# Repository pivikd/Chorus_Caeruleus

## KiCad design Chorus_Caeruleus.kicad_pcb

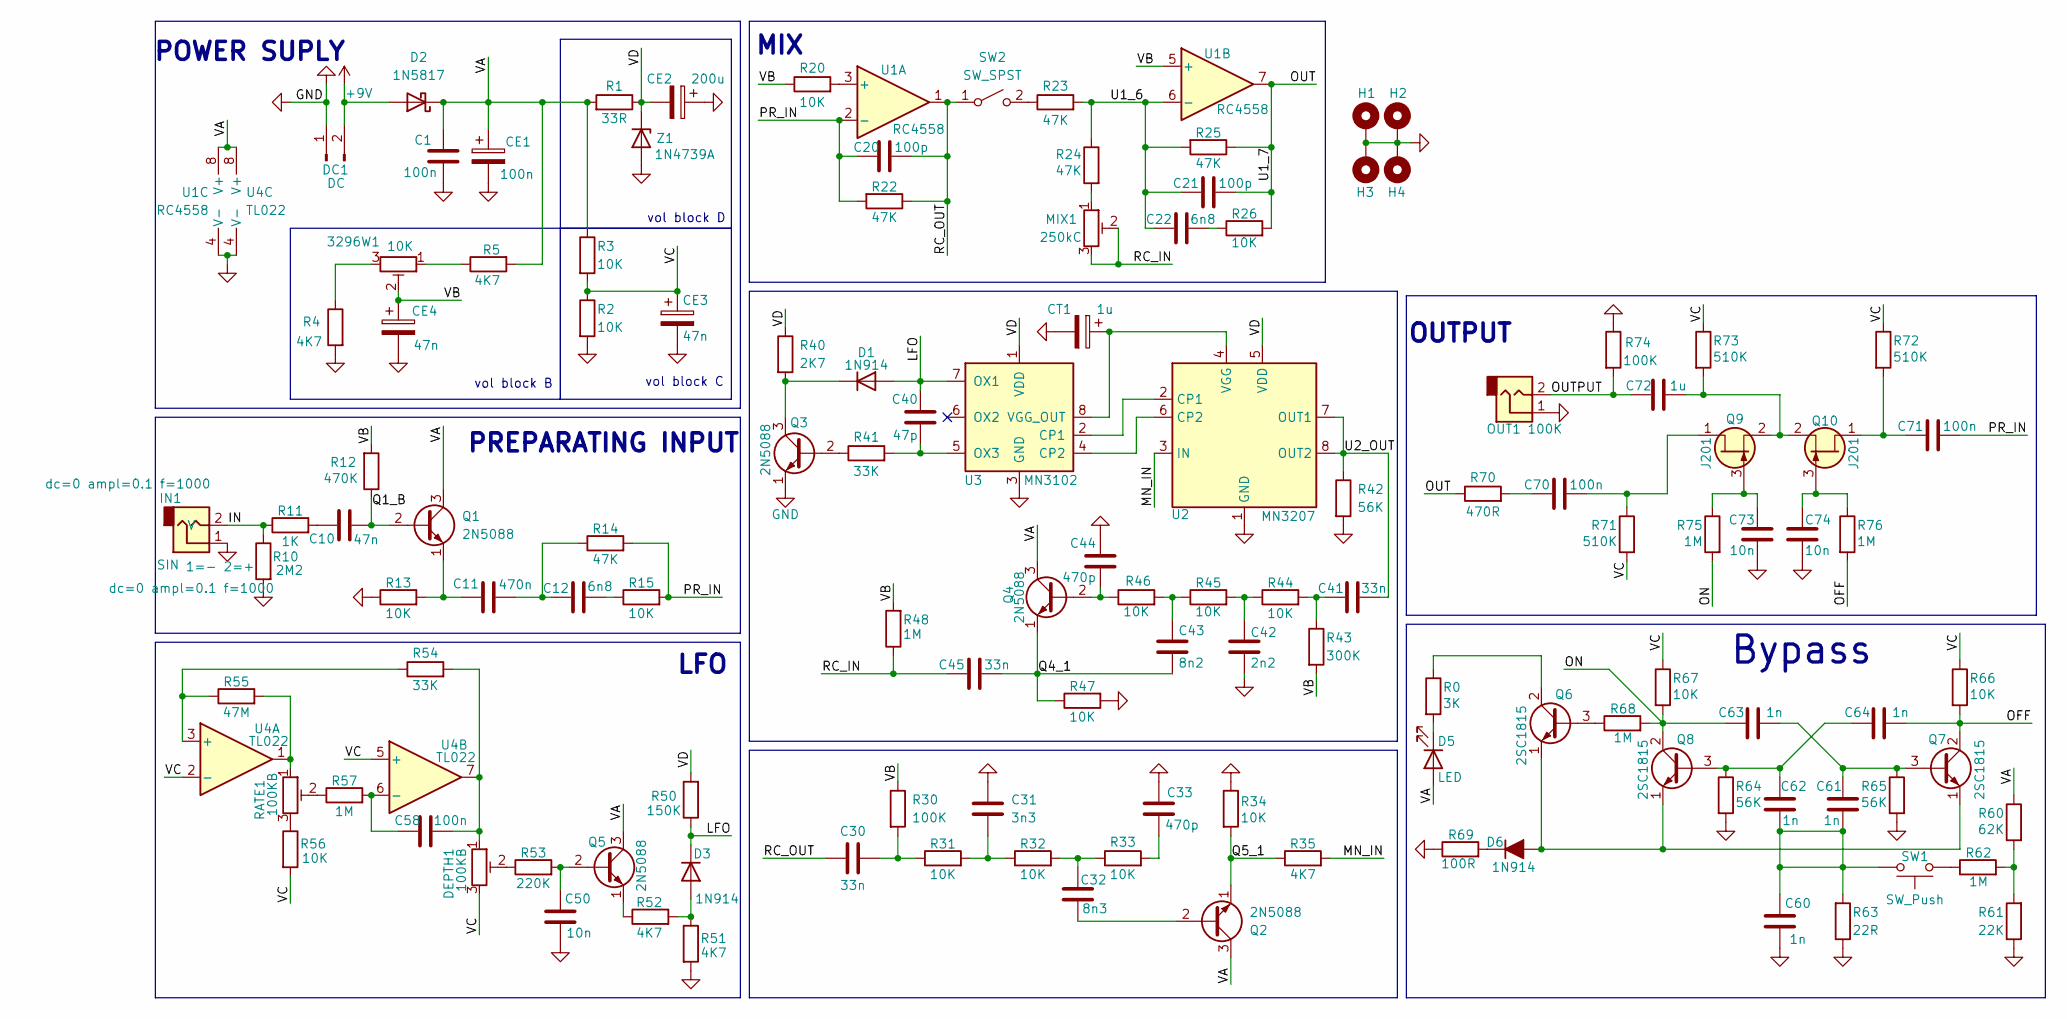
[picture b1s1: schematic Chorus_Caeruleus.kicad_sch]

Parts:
3296W1: 10K; Potentiometer_Bourns_3296W_Vertical
C1, C58, C70, C71: 100n; C_disc_D7_W2.5_P5
C10: 47n; C_Disc_D4.3_W1.9_P5.00
C11: 470n; C_disc_D7_W2.5_P5
C12, C22: 6n8; C_Disc_D4.3_W1.9_P5.00
C20, C21: 100p; C_Disc_D4.3_W1.9_P5.00
C30, C41, C45: 33n; C_Disc_D4.3_W1.9_P5.00
C31: 3n3; C_Disc_D4.3_W1.9_P5.00
C32: 8n3; C_Disc_D4.3_W1.9_P5.00
C33, C44: 470p; C_Disc_D4.3_W1.9_P5.00
C40: 47p; C_Disc_D4.3_W1.9_P5.00
C42: 2n2; C_Disc_D4.3_W1.9_P5.00
C43: 8n2; C_Disc_D4.3_W1.9_P5.00
C50, C73, C74: 10n; C_Disc_D4.3_W1.9_P5.00
C60, C61, C62, C63, C64: 1n; C_Disc_D4.3_W1.9_P5.00
C72: 1u; C_Disc_D4.3_W1.9_P5.00
CE1: 100n; CP_Radial_D4.0mm_P1.50mm
CE2: 200u; CP_Radial_D6.3mm_P2.50mm
CE3, CE4: 47n; CP_Radial_D4.0mm_P1.50mm
CT1: 1u; CP_Radial_Tantal_D5.0mm_P2.50mm
D1, D3, D6: 1N914; D_DO-35_SOD27_P7.62mm_Horizontal
D2: 1N5817; D_DO-41_SOD81_P10.16mm_Horizontal
D5: LED; PinHeader_1x02_P2.00mm_Vertical
DC1: DC; PinSocket_1x02_P2.00mm_Vertical
DEPTH1: 100KB; TO-92S
H1, H2, H3, H4: MountingHole_Pad; MountingHole_3.2mm_M3_ISO14580_Pad
IN1: dc=0 ampl=0.1 f=1000; PinHeader_1x02_P2.00mm_Vertical
MIX1: 250kC; TO-92S
OUT1: 100K; PinHeader_1x02_P2.00mm_Vertical
Q1, Q2, Q3, Q4, Q5: 2N5088; TO-92_Inline
Q6, Q7, Q8: 2SC1815; TO-92_Inline
Q9, Q10: J201; TO-92
R0: 3K; R_Axial_DIN0207_L6.3mm_D2.5mm_P7.62mm_Horizontal
R1: 33R; R_Axial_DIN0207_L6.3mm_D2.5mm_P7.62mm_Horizontal
R2, R3, R13, R15, R20, R26, R31, R32, R33, R34, R44, R45, R46, R47, R56, R66, R67: 10K; R_Axial_DIN0207_L6.3mm_D2.5mm_P7.62mm_Horizontal
R4, R5, R35, R51, R52: 4K7; R_Axial_DIN0207_L6.3mm_D2.5mm_P7.62mm_Horizontal
R10: 2M2; R_Axial_DIN0207_L6.3mm_D2.5mm_P7.62mm_Horizontal
R11: 1K; R_Axial_DIN0207_L6.3mm_D2.5mm_P7.62mm_Horizontal
R12: 470K; R_Axial_DIN0207_L6.3mm_D2.5mm_P7.62mm_Horizontal
R14, R22, R23, R24, R25: 47K; R_Axial_DIN0207_L6.3mm_D2.5mm_P7.62mm_Horizontal
R30, R74: 100K; R_Axial_DIN0207_L6.3mm_D2.5mm_P7.62mm_Horizontal
R40: 2K7; R_Axial_DIN0207_L6.3mm_D2.5mm_P7.62mm_Horizontal
R41, R54: 33K; R_Axial_DIN0207_L6.3mm_D2.5mm_P7.62mm_Horizontal
R42, R64, R65: 56K; R_Axial_DIN0207_L6.3mm_D2.5mm_P7.62mm_Horizontal
R43: 300K; R_Axial_DIN0207_L6.3mm_D2.5mm_P7.62mm_Horizontal
R48, R57, R62, R68, R75, R76: 1M; R_Axial_DIN0207_L6.3mm_D2.5mm_P7.62mm_Horizontal
R50: 150K; R_Axial_DIN0207_L6.3mm_D2.5mm_P7.62mm_Horizontal
R53: 220K; R_Axial_DIN0207_L6.3mm_D2.5mm_P7.62mm_Horizontal
R55: 47M; R_Axial_DIN0207_L6.3mm_D2.5mm_P7.62mm_Horizontal
R60: 62K; R_Axial_DIN0207_L6.3mm_D2.5mm_P7.62mm_Horizontal
R61: 22K; R_Axial_DIN0207_L6.3mm_D2.5mm_P7.62mm_Horizontal
R63: 22R; R_Axial_DIN0207_L6.3mm_D2.5mm_P7.62mm_Horizontal
R69: 100R; R_Axial_DIN0207_L6.3mm_D2.5mm_P7.62mm_Horizontal
R70: 470R; R_Axial_DIN0207_L6.3mm_D2.5mm_P7.62mm_Horizontal
R71, R72, R73: 510K; R_Axial_DIN0207_L6.3mm_D2.5mm_P7.62mm_Horizontal
RATE1: 100KB; TO-92S
SW1: SW_Push; PinSocket_1x02_P2.00mm_Vertical
SW2: SW_SPST; PinSocket_1x02_P2.00mm_Vertical
U1: RC4558; DIP-8_W7.62mm
U2: MN3207; DIP-8_W7.62mm
U3: MN3102; DIP-8_W7.62mm
U4: TL022; DIP-8_W7.62mm
Z1: 1N4739A; D_DO-41_SOD81_P10.16mm_Horizontal

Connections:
+9V: D2.2 (A), DC1.2
/IN: IN1.2, R10.1, R11.1
/LFO: C40.1, D1.2 (A), D3.1 (K), R50.1, U3.7 (OX1)
/MN_IN: R35.2, U2.3 (IN)
/OFF: C64.2, Q7.2 (C), R66.2, R76.2
/ON: C63.1, Q8.2 (C), R67.2, R68.2, R75.2
/OUT: C21.2, R25.1, R26.2, R70.1, U1.7
/OUTPUT: C72.1, OUT1.2, R74.2
/PR_IN: C20.1, C71.2, R14.2, R15.2, R22.2, U1.2 (-)
/Q1_B: C10.2, Q1.2 (B), R12.1
/Q4_1: C43.2, C45.2, Q4.1 (E), R47.1
/Q5_1: Q2.1 (E), R34.2, R35.1
/RC_IN: C45.1, MIX1.2, MIX1.3, R48.1
/RC_OUT: C20.2, C30.1, R22.1, SW2.1 (A), U1.1
/U1_6: C21.1, C22.1, R23.2, R24.1, R25.2, U1.6 (-)
/U2_OUT: C41.2, R42.1, U2.7 (OUT1), U2.8 (OUT2)
/VA: C1.1, CE1.1, D2.1 (K), D5.2 (A), Q1.3 (C), Q2.3 (C), Q4.3 (C), Q5.3 (C), R1.2, R3.1, R5.2, R60.1, U1.8 (V+), U4.8 (V+)
/VB: 3296W1.2, CE4.1, R12.2, R20.1, R30.1, R43.2, R48.2, U1.5 (+)
/VC: CE3.1, DEPTH1.3, R2.1, R3.2, R56.2, R66.1, R67.1, R71.2, R72.1, R73.1, U4.2 (-), U4.5 (+)
/VD: CE2.2, R1.1, R40.1, R50.2, U2.5 (VDD), U3.1 (VDD), Z1.1 (K)
GND: C1.2, C31.1, C33.1, C42.2, C44.1, C50.2, C60.2, C73.1, C74.1, CE1.2, CE2.1, CE3.2, CE4.2, CT1.2, DC1.1, H1.1 (1_1), H2.1 (1_1), H3.1 (1_1), H4.1 (1_1), IN1.1, OUT1.1, Q3.1 (E), R2.2, R4.2, R10.2, R13.1, R34.1, R42.2, R47.2, R51.2, R61.1, R63.1, R64.2, R65.2, R69.1, R74.1, U1.4 (V-), U2.1 (GND), U3.3 (GND), U4.4 (V-), Z1.2 (A)
unnamed: 3296W1.1, R5.1
unnamed: 3296W1.3, R4.1
unnamed: C10.1, R11.2
unnamed: C11.2, C12.1, R14.1
unnamed: C12.2, R15.1
unnamed: C22.2, R26.1
unnamed: C30.2, R30.2, R31.1
unnamed: C31.2, R31.2, R32.1
unnamed: C32.1, R32.2, R33.1
unnamed: C33.2, R33.2
unnamed: C41.1, R43.1, R44.2
unnamed: C42.1, R44.1, R45.2
unnamed: C43.1, R45.1, R46.2
unnamed: C58.2, DEPTH1.1, R54.2, U4.7
unnamed: C60.1, C61.1, C62.1, R63.2, SW1.2
unnamed: C70.1, R70.2
unnamed: D1.1 (K), Q3.3 (C), R40.2
unnamed: D3.2 (A), R51.1, R52.2
unnamed: D5.1 (K), R0.2
unnamed: D6.2 (A), Q6.1 (E), Q7.1 (E), Q8.1 (E)
unnamed: D6.1 (K), R69.2
unnamed: DEPTH1.2, R53.1
unnamed: MIX1.1, R24.2
unnamed: C11.1, Q1.1 (E), R13.2
unnamed: C32.2, Q2.2 (B)
unnamed: Q3.2 (B), R41.1
unnamed: C44.2, Q4.2 (B), R46.1
unnamed: C50.1, Q5.2 (B), R53.2
unnamed: Q5.1 (E), R52.1
unnamed: Q6.3 (B), R68.1
unnamed: Q6.2 (C), R0.1
unnamed: C61.2, C63.2, Q7.3 (B), R65.1
unnamed: C62.2, C64.1, Q8.3 (B), R64.1
unnamed: C70.2, Q9.1 (D), R71.1
unnamed: C73.2, Q9.3 (G), R75.1
unnamed: C71.1, Q10.1 (D), R72.2
unnamed: C74.2, Q10.3 (G), R76.1
unnamed: C72.2, Q9.2 (S), Q10.2 (S), R73.2
unnamed: R55.2, RATE1.1, U4.1
unnamed: R56.1, RATE1.3
unnamed: R57.1, RATE1.2
unnamed: R60.2, R61.2, R62.2
unnamed: R62.1, SW1.1
unnamed: R23.1, SW2.2 (B)
unnamed: R20.2, U1.3 (+)
unnamed: U2.2 (CP1), U3.2 (CP1)
unnamed: U2.6 (CP2), U3.4 (CP2)
unnamed: CT1.1, U2.4 (VGG), U3.8 (VGG_OUT)
unnamed: C40.2, R41.2, U3.5 (OX3)
unnamed: R54.1, R55.1, U4.3 (+)
unnamed: C58.1, R57.2, U4.6 (-)

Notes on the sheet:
LFO
vol block D
OUTPUT
PREPARATING INPUT
MIX
POWER SUPLY
Bypass
vol block B
vol block C

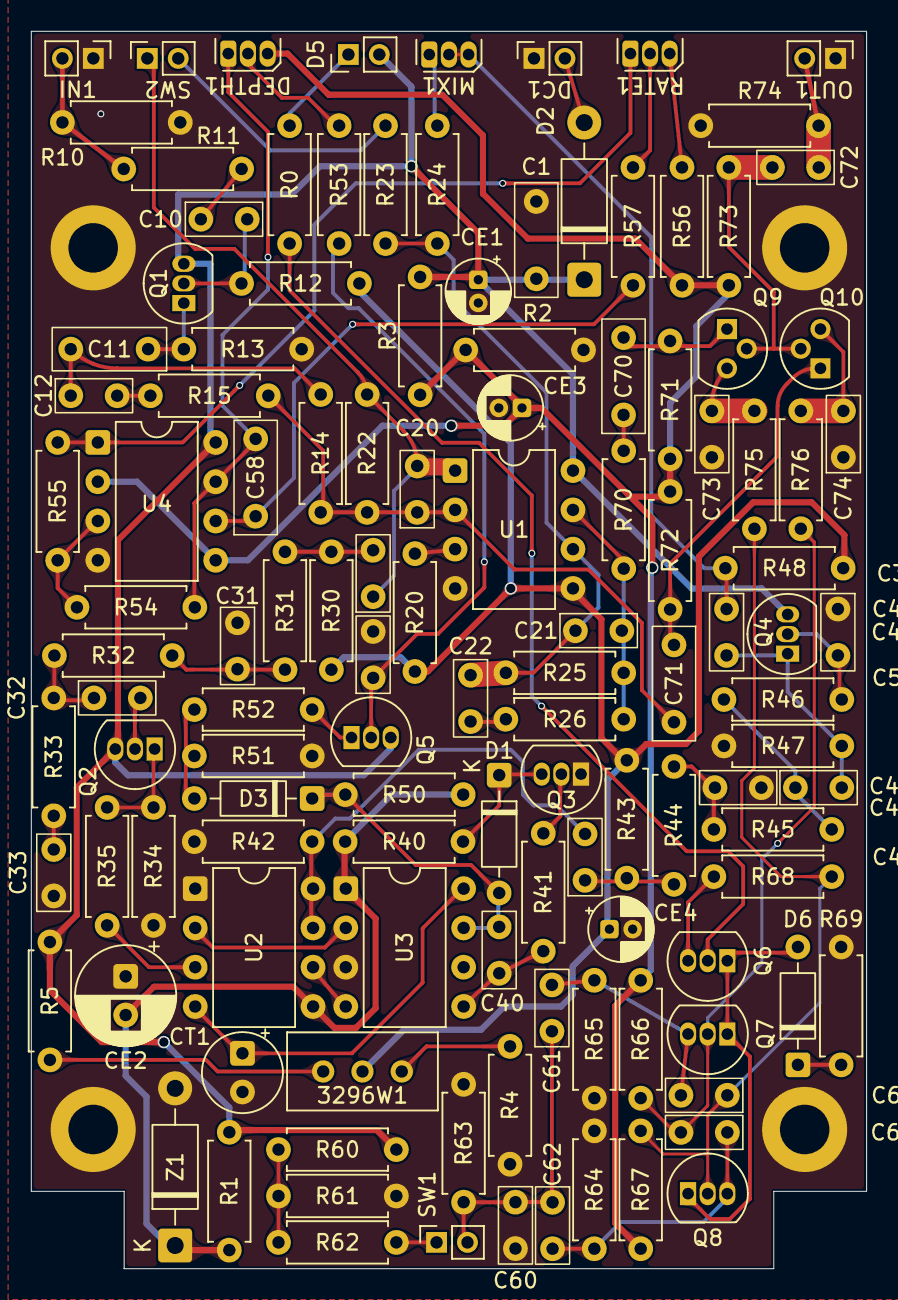
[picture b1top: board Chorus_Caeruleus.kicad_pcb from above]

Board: 2 copper layers, 54.0 x 80.0 mm, 125 parts (0 on the bottom side), 72 nets.
